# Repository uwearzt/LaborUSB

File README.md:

# LaborUSB

Adapter for Labor Power Supply to USB i.e. for Raspberry Pi.

The USB connector from the Sparkfun Eagle Library  was used to create the USB
connector for this Library, see
<https://github.com/sparkfun/SparkFun-Eagle-Libraries>

## Overview

Many prototyping boards these days use USB Connectors as Power Source. For easy powering those devices with my DC Power
Supply (or in german "Labornetzteil") i created a adaptor from 4 mm banana plugs to 4 USB Jacks.

Additional benefit is that all types of iThings can be loaded with the Adaptor. The necessary research for loading Apple
devices was done by [Adafruit](https://www.adafruit.com), see their page
about [icharging](https://learn.adafruit.com/minty-boost/icharging).

The device in action:

Find all the files necessary to build your own on [GitHub](https://github.com/uwearzt/LaborUSB.git).

I have a few boards available, if you like to build your own, contact me.

<!-- more -->

## Design

### Schematic

The design is really simple and consists of only 4 resistors and 8 jacks. The real work was to make the mechanical dimensions fit for easy and fast assembly.

### Board

Can be easily done by every board house.

## Bill of materials

<table>
	<thead>
		<tr><th>Count</th><th>Description</th><th>Source</th></tr>
	</thead>
	<tbody>
		<tr><td>2</td><td>Through-hole banana jack Black</td><td><a href="https://www.reichelt.de">Reichelt</a></td></tr>
		<tr><td>2</td><td>Through-hole banana jack Red</td><td><a href="https://www.reichelt.de">Reichelt</a></td></tr>
		<tr><td>1</td><td>Resistor 43K 0805</td><td><a href="https://www.distrelec.de">Distrelec</a></td></tr>
		<tr><td>1</td><td>Resistor 75K 0805</td><td><a href="https://www.distrelec.de">Distrelec</a></td></tr>
		<tr><td>2</td><td>Resistor 51K 0805</td><td><a href="https://www.distrelec.de">Distrelec</a></td></tr>
		<tr><td>4</td><td>USB Jack</td><td><a href="https://www.distrelec.de">Distrelec</a></td></tr>
		<tr><td>1</td><td>Laser cut Front panel 3mm thick</td><td><a href="http://www.formulor.de">Formulor</a></td></tr>
		<tr><td>1</td><td>Laser cut Back panel 3mm thick</td><td><a href="http://www.formulor.de">Formulor</a></td></tr>
		<tr><td>4</td><td>Nuts 6mm Fine Pitch Thread</td><td></td></tr>
		<tr><td>4</td><td>Screws M3 * 6mm</td><td></td></tr>
		<tr><td>4</td><td>Screws M3 * 10mm</td><td></td></tr>
		<tr><td>4</td><td>Hex Standoffs M3 * 12mm without Thread</td><td></td></tr>
		<tr><td>4</td><td>Hex Standoffs * 5mm with Thread</td><td></td></tr>
	</tbody>
</table>

## Assembly

### Solder Resistors

### Prepare Front Panel

Place the banana jacks in the front panel and secure them with the additional 6mm fine thread nuts. Add one of the delivered 6mm fine thread nuts to every banana plug.

Add the 12mm standoff to the front panel with the M3 10mm screws. If you do not have 12mm standoffs, it is possible to replace the 12mm standoffs with a 10mm standoffs and a additional nuts.

### Add board to front panel

Place the board on the 12 mm standoff and secure it with the 5mm standoffs.

Screw the 6mm nut up until the board is reached.

Take the remaining 6mm fine threaded nuts and secure the banana plugs on the board.

### Add USB Jacks

With the USB jacks from Reichelt, you need to first straighten the outer pins as seen on the left jack. Otherwise they will not fit through the front panel.

Place all 4 USB Jacks in the front panel and solder them to the board.

### Add back panel

Use the 4 M3*6 screws and screw the backpanel in place.

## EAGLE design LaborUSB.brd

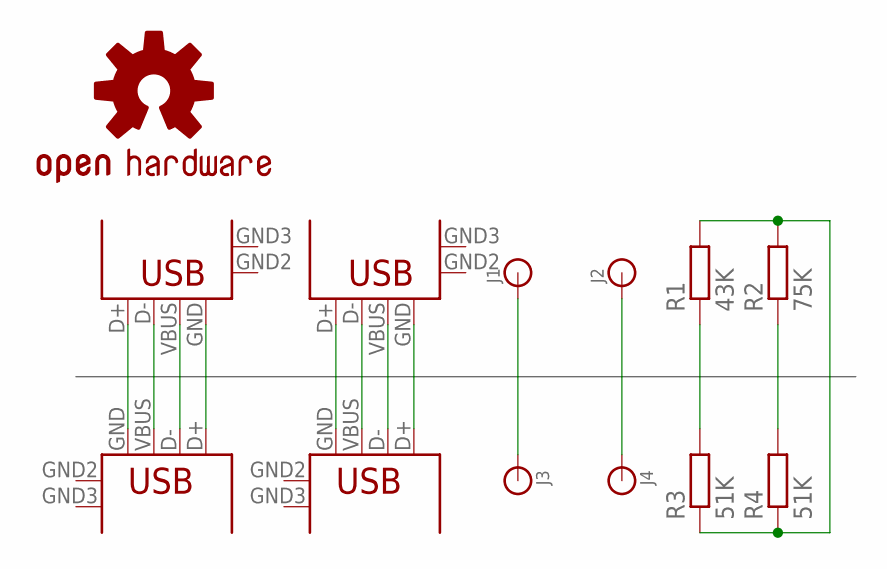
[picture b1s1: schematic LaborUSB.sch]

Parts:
J1, J2, J3, J4: BANANA
LOGO1: OSHW-LOGOM; OSHW-LOGO-M
R1: 43K; R0805
R2: 75K; R0805
R3, R4: 51K; R0805
USB1, USB2, USB3, USB4: USB+SHIELD; USB-A-VERTICAL

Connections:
D+: R2.1, R4.2, USB1.D+, USB2.D+, USB3.D+, USB4.D+
D-: R1.1, R3.2, USB1.D-, USB2.D-, USB3.D-, USB4.D-
GND: J1.P$1, J2.P$1, R3.1, R4.1, USB1.GND, USB2.GND, USB3.GND, USB4.GND
VBUS: J3.P$1, J4.P$1, R1.2, R2.2, USB1.VBUS, USB2.VBUS, USB3.VBUS, USB4.VBUS

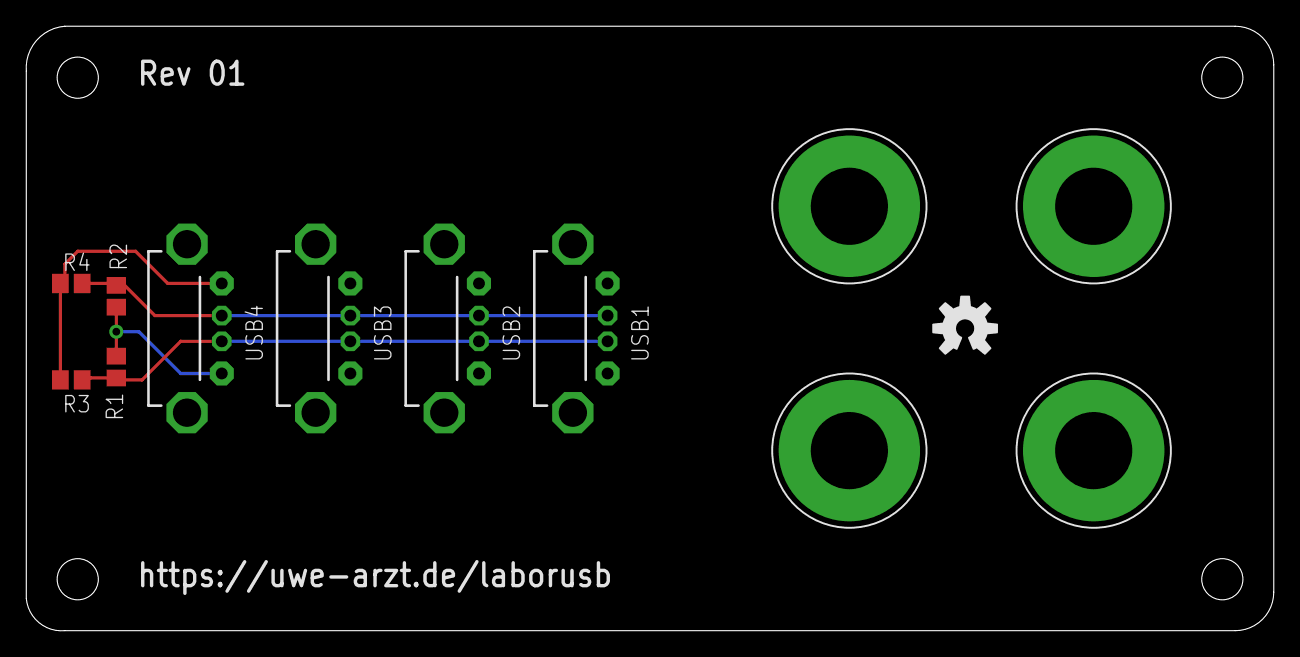
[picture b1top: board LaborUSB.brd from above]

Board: 2 copper layers, 97.0 x 47.0 mm, 13 parts (0 on the bottom side), 4 nets.

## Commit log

2013-09-08 Datasheets and Case
2013-09-09 First board to check Library
2013-09-09 Added iPhone charge capabilty, Component Names
2013-09-09 First prototype order
2013-09-10 Fix in thermals on Banana Plug
2013-10-05 Added Adobe Illustrator file for Formulor
2014-02-01 changed license to BSD
2014-05-26 added Datasheet for banana plug
2014-07-22 PDFs after public request
2014-09-22 ignore checksum files (*.ic)
2019-06-28 move instructions into repo

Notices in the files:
parts and their libraries:
SparkFun-Aesthetics: Licensing: CC v3.0 Share-Alike You are welcome to use this library for commercial purposes.
